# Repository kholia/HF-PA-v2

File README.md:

### HF-PA-v2

VU3CER's `Class-E HF PA` for https://github.com/kholia/Easy-Digital-Beacons-v1
project for 20m band and up. It has (optional) software-controlled variable PA
Output Power.

Supported bands: 80, 60, 40, 30, 20, 17m, and more bands with switchable 'LPF
Module' board.

(July 2021 Update): While this HF PA works as well as the uSDX V1.02 PA and the
QCX+ PA (they all use the same design!), we prefer our new [HF-PA-v3
system](https://github.com/kholia/HF-PA-v3/) PA for its robustness. If you
need a 3W+ @ 14 MHz with high efficiency, this Class-E HF PA design
(`HF-PA-v2`) is the best one ;)

Constraints for the initial PCB prototypes for validating the design:

- PCB is to be homebrewed (laser printer, toner tranfer using iron, etching via FeCl3)

- PCB is single-sided. Only one layer is available for routing.

- BS170 MOSFETs need to be on an edge to allow usage of heatsinks.

- My external `PA150 HF Linear Amplifier` needs 2W minimum to function.

Input: Few milliwatts is fine. Note: Si5351's output is around 8-10mW.

Output: Full-power 3.2W+ @ 13.3v (4S LiFePo4) for 20m band (14.074 MHz) with
around 45-55% efficiency *OR* Safer 2W with reasonable PWM setting for digital
modes!

Note: All screenshots are clickable and zoomable.

Note 2: Active cooling (fan) is recommended for digital modes! You have been
informed ;)

Schematic:

The HF PA has over-voltage ("High-SWR") protection via a `47v zener power-dumping diode`.

PCB renderings:

Socketable version (recommended):

Testing the Triple-Mode PSU + LPF 20m + 3xBS170 @ 13.8v:

LPF schematic (from uSDX PCB by WB2CBA):

Safe power supply module for the PA. It has over-current protection.

Note: This 3D rendering is *only* published to help with the manual layout work
on Zero-PCBs.

Note 2: Various sub-circuits were simulated in LTspice prior to implementation.

### Sample Code

- https://github.com/kholia/uSDX_Beacon

- https://github.com/kholia/Easy-Digital-Beacons-v1

#### O(Current consumption)

The ESP8266 usually draws a peak current of about 250mA after it wakes up and
then more or less constantly draws around 70mA before it goes back to sleep.

DS3231 -> 5mA

Si5351 -> ~50 to 100mA

Upper bound -> 1.4A maximum.

#### BOM

- 1 x SN74ACT00N (TI)

- 3 x BS170 (ON Semi)

- 1 x 7805 Voltage Regulator TO-220 (STMicroelectronics)

- 1 x 7806 Voltage Regulator TO-220 (STMicroelectronics)

- 1 x 1N5822

- 1 x 1N5368B (47V 5W Zener Diode)

- 2 x 0.2 Ohms - 3W Current Sensing Resistor

- 2 x 1k Ohm - 0.25W Metal Film Resistor

- 220uF 25v Electrolytic Capacitor

- 5 x 100nF (104) Ceramic Capacitor

- 1 x 10nF (103) Ceramic Capacitor

- 1 x BD140 Transistor

- 1 x TIP42 Darlington Transistor

- 3 x T37-6 - Yellow Toroid, 1 x T37-2 - Red Toroid (LPF)

- 2 x 180pf, 2 x 390pf, 1 x 30pF NP0 Ceramic Capacitors (LPF caps, Kemet)

- 3 meters - Copper Magnetic Winding Wire (24 AWG - 25 SWG)

- Misc: Connectors, Zero PCB, Various Consumables

- Tools: LCR-T4 Meter (for measuring things), RF Power Meter

Tip: Buy in bulk for better pricing, and for getting spares for the "junk box".

#### 20m LPF Module Details

- L1 - T37-6 / 16 turns
- L2 - T37-6 / 17 turns
- L3 - T37-6 / 16 turns
- L4 - T37-2 / 10 turns
- C1 - 180pf
- C2 - 390pf
- C3 - 390pf
- C4 - 180pf
- C5 - 30pf

Borrowed from QCX manual and uSDX WB2CBA PCB documentation.

#### BOM + Equipment Sources

- https://www.semikart.com/ (BS170, NP0 LPF caps - Kemet and others, Aavid DIP-14/16 Heat Sinks)

- https://www.semikart.com/search/SN74ACT00N

- https://robu.in/product/0-2-ohm-3w-surface-mount-sense-resistor-pack-of-3/

- https://www.electronicscomp.com/

  - BS170, regular caps, ST voltage regulators

  - TIP42, BD140

- https://www.electroncomponents.com/ (transistors, connectors, consumables, misc)

- https://www.sunrom.com/ (regular ceramic caps)

- https://projectpoint.in/

  - Transistors, regular caps, voltage regulators, MFR resistors, misc

  - Copper Magnetic Winding Wire

- https://www.bhagwatilightingindustries.com (Thermal Adhesive Paste)

- https://www.sunrom.com/p/254mm-40x1-female-socket-strip-machine-round-pins

  `SIP Sockets 1A`

- eBay (`gr_makis`) - Toroids

- [LCR-T4 LCR Meter](https://www.techtonics.in/lcr-t4-12864-lcd-graphical-transistor-tester-resistance-capacitance-esr-scr-meter)

### Notes

- The `CDIL 2N3904` TO-92 transistor has `CT2N 3904 LS` marking on it.

  `CT` -> `Continental... Device India Ltd (CDIL)`

- `Burnt` BS170 MOSFETs typically have their `Drain` and `Gate` shorted (Pin 1 and Pin 2 respectively).

- Use `SIP sockets` to avoid accidentally killing the MOSFETs via ESD (during probing, soldering, etc).

- PCB test: Remove the MOSFETS (keep everything else connected) and measure the
  resistance between the `Gate Pin` and `Ground`. It should show `OL (Open Line)`.

### Tips

- BS170 MOSFETs are very sensitive with regards to ESD and high soldering
  temperatures.

  Use best practices when dealing with BS170 MOSFETs and perhaps always ;)

#### References

- https://github.com/kholia/uSDX_Beacon
- https://github.com/agustinmartino/wsjt_transceiver
- http://hyse.org/pdf/www.aoc.nrao.edu/~pharden/hobby/_ClassDEF1.pdf
- http://hyse.org/pdf/www.aoc.nrao.edu/~pharden/hobby/_ClassDEF2.pdf
- http://thestone.zone/radio/2020/12/13/multi-watt-amplifier.html
- http://thestone.zone/radio/2020/12/18/gate-driver-amplifier.html
- http://thestone.zone/radio/2021/01/14/capacitors.html
- http://thestone.zone/radio/2021/01/16/minor-enhancements.html
- https://www.g0kla.com/scpa/SimpleCheapPA.php
- https://www.linkedin.com/pulse/rf-pcb-design-rules-manufacturing-process-lisa-chu/
- http://thestone.zone/radio/2021/06/04/attenuator.html
- http://thestone.zone/radio/2021/06/05/power-amplifier.html
- https://on7dq.blogspot.com/2020/12/qcx-mini-measurements.html
- https://www.random-science-tools.com/electronics/dBm-Watts-volts.htm
- https://www.mitsubishielectric.com/semiconductors/php/oSearch.php?FOLDER=/product/highfrequency/siliconrf/discrete
- http://www.carnut.info/WSPR_Tx/WSPR_Tx.htm
- https://sites.google.com/view/andy-g0ftd/iron-fist-transmitter
- https://www.dj0abr.de/english/technik/dds/pa.htm
- https://www.qsl.net/py2ohh/
- https://hf5l.pl/en/transceiver-usdx-with-arduino-nano/#

#### Credits

- MTR5B schematic
- PFR-3 design
- Dan Tayloe, N7VE (NC2030 PA design)
- Hans Summers (QCX+)
- Guido PE1NNZ (uSDX)
- WB2CBA (uSDX PCB)
- Tom (AK2B)
- Various uSDX folks
- Chris (G0KLA / AC2CZ) - over-current protection

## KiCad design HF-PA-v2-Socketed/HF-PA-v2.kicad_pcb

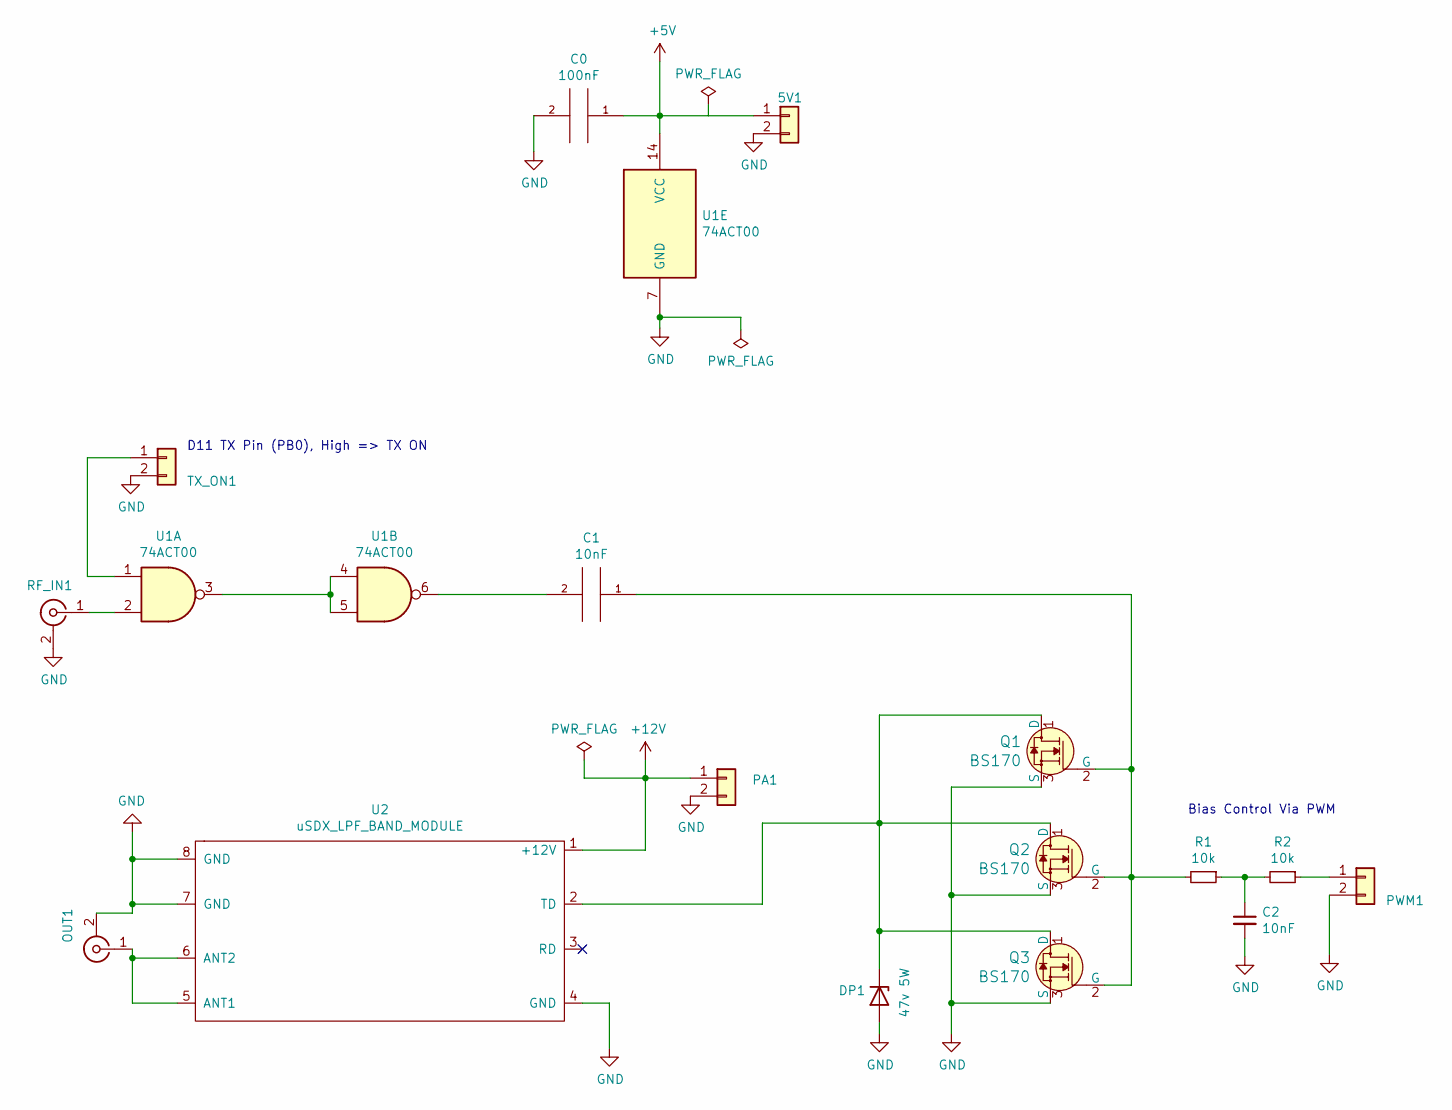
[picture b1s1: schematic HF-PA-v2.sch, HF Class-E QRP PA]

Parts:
5V1: Conn_01x02; PinHeader_1x02_P2.54mm_Vertical
C0: 100nF; C_Disc_D4.3mm_W1.9mm_P5.00mm
C1, C2: 10nF; C_Disc_D4.3mm_W1.9mm_P5.00mm
DP1: 47v 5W; D_DO-201_P5.08mm_Vertical_AnodeUp
OUT1: Conn_Coaxial; SMA_Samtec_SMA-J-P-X-ST-EM1_EdgeMount
PA1: Conn_01x02; PinHeader_1x02_P2.54mm_Vertical
PWM1: Conn_01x02; PinHeader_1x02_P2.54mm_Vertical
Q1, Q2, Q3: BS170; PinSocket_1x03_P2.54mm_Vertical; MPN BS170; Digi-Key_PN BS170-ND
R1, R2: 10k; R_Axial_DIN0204_L3.6mm_D1.6mm_P2.54mm_Vertical
RF_IN1: Conn_Coaxial; SMA_Amphenol_901-144_Vertical
TX_ON1: Conn_01x02; PinHeader_1x02_P2.54mm_Vertical
U1: 74ACT00; DIP-14_W7.62mm_LongPads
U2: uSDX_LPF_BAND_MODULE; uSDX_LPF_Band_Module

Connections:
+5V: 5V1.1, C0.1, U1.14 (VCC)
+12V: PA1.1, U2.1 (+12V)
GND: 5V1.2, C0.2, C2.2, DP1.2 (A), OUT1.2 (Ext), PA1.2, PWM1.2, Q1.3 (S), Q2.3 (S), Q3.3 (S), RF_IN1.2 (Ext), TX_ON1.2, U1.7 (GND), U2.4 (GND), U2.7 (GND), U2.8 (GND); also elsewhere on the board
unnamed 3: C1.1, Q1.2 (G), Q2.2 (G), Q3.2 (G), R1.2; also elsewhere on the board
unnamed: C1.2, U1.6
unnamed: C2.1, R1.1, R2.2
unnamed 6: DP1.1 (K), Q1.1 (D), Q2.1 (D), Q3.1 (D), U2.2 (TD); also elsewhere on the board
unnamed: OUT1.1 (In), U2.5 (ANT1), U2.6 (ANT2)
unnamed: PWM1.1, R2.1
unnamed: RF_IN1.1 (In), U1.2
unnamed: TX_ON1.1, U1.1
unnamed: U1.3, U1.4, U1.5

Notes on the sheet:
D11 TX Pin (PB0), High => TX ON
Bias Control Via PWM

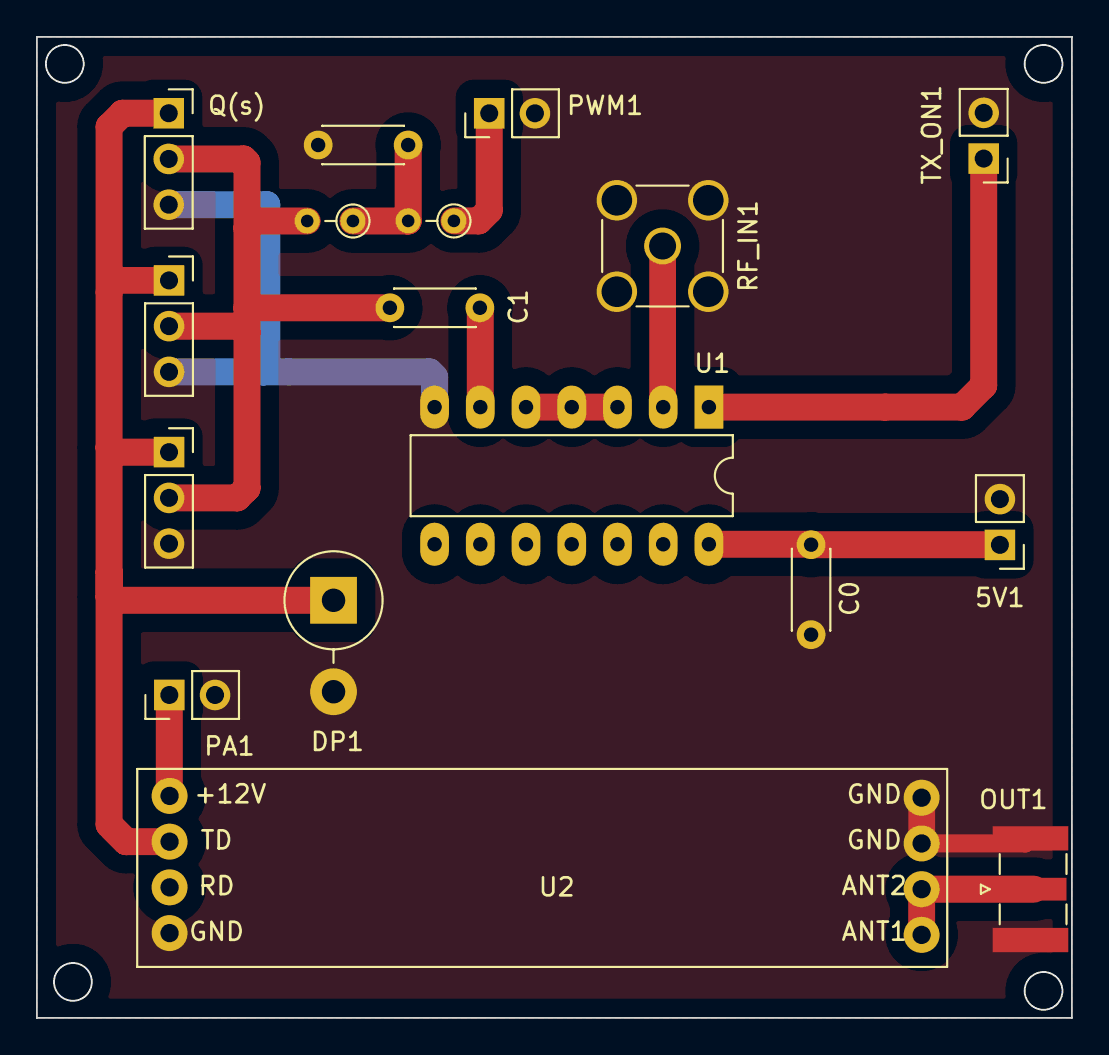
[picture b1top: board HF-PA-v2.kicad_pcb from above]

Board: 2 copper layers, 57.5 x 54.5 mm, 17 parts (0 on the bottom side), 12 nets.

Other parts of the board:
Q(s): BS170; PinSocket_1x03_P2.54mm_Vertical

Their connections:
GND: Q(s).3; also elsewhere on the board
unnamed 3: Q(s).2; also elsewhere on the board
unnamed 6: Q(s).1; also elsewhere on the board

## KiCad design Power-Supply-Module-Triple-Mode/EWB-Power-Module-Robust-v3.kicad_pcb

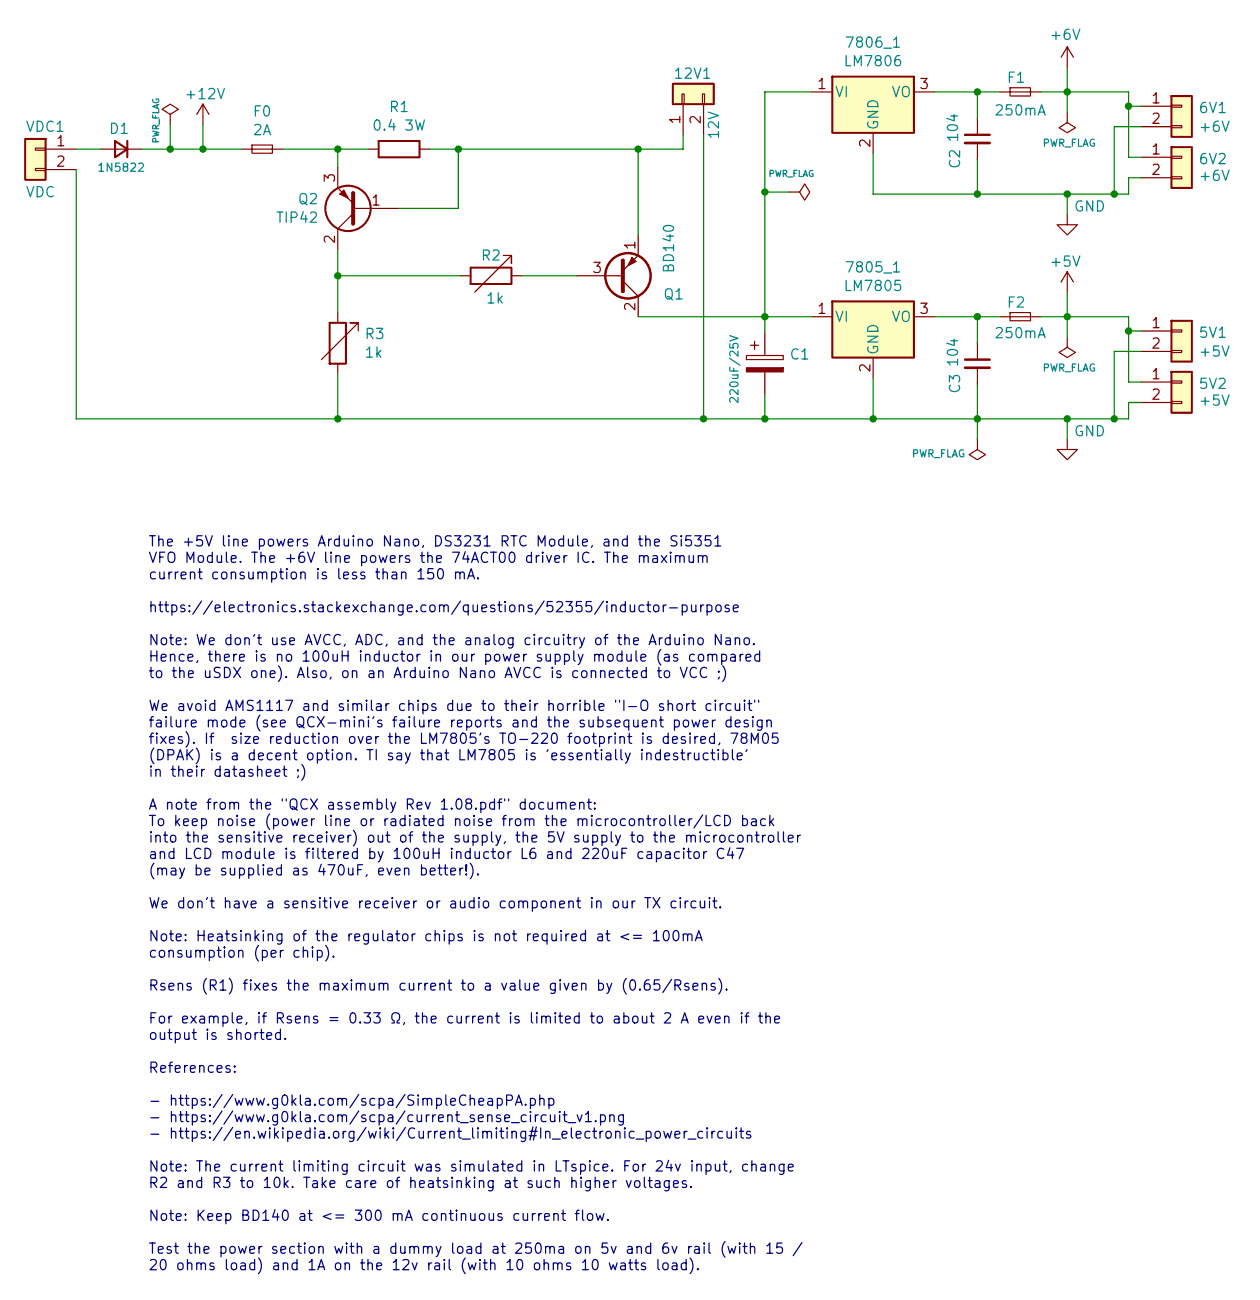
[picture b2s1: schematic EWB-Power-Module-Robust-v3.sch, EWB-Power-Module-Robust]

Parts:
5V1, 5V2: +5V; PinHeader_1x02_P2.54mm_Vertical
6V1, 6V2: +6V; PinHeader_1x02_P2.54mm_Vertical
12V1: 12V; PinHeader_1x02_P2.54mm_Vertical
7805_1: LM7805; TO-220-3_Vertical
7806_1: LM7806; TO-220-3_Vertical
C1: 220uF/25V; CP_Radial_D5.0mm_P2.50mm
C2, C3: 104; C_Disc_D3.4mm_W2.1mm_P2.50mm
D1: 1N5822; D_DO-201AD_P3.81mm_Vertical_KathodeUp
F0: 2A; Fuse_BelFuse_0ZRE0025FF_L9.6mm_W3.8mm
F1, F2: 250mA; Fuse_BelFuse_0ZRE0025FF_L9.6mm_W3.8mm
Q1: BD140; TO-126-3_Vertical
Q2: TIP42; TO-220-3_Vertical
R1: 0.4 3W; R_2512_6332Metric_Pad1.40x3.35mm_HandSolder
R2, R3: 1k; R_Axial_DIN0207_L6.3mm_D2.5mm_P5.08mm_Vertical
VDC1: VDC; PinHeader_1x02_P2.54mm_Vertical

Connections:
+5V: 5V1.1, 5V2.1, F2.2
+6V: 6V1.1, 6V2.1, F1.2
+12V: D1.1 (K), F0.1
GND: 5V1.2, 5V2.2, 6V1.2, 6V2.2, 12V1.2, 7805_1.2 (GND), 7806_1.2 (GND), C1.2, C2.2, C3.2, R3.2, VDC1.2
unnamed: 12V1.1, Q1.1 (E), Q2.1 (B), R1.1
unnamed: 7805_1.1 (VI), 7806_1.1 (VI), C1.1, Q1.2 (C)
unnamed: 7805_1.3 (VO), C3.1, F2.1
unnamed: 7806_1.3 (VO), C2.1, F1.1
unnamed: D1.2 (A), VDC1.1
unnamed: F0.2, Q2.3 (E), R1.2
unnamed: Q1.3 (B), R2.1
unnamed: Q2.2 (C), R2.2, R3.1

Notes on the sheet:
The +5V line powers Arduino Nano, DS3231 RTC Module, and the Si5351 VFO Module. The +6V line powers the 74ACT00 driver IC. The maximum current consumption is less than 150 mA. https://electronics.stackexchange.com/questions/52355/inductor-purpose Note: We don't use AVCC, ADC, and the analog circuit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

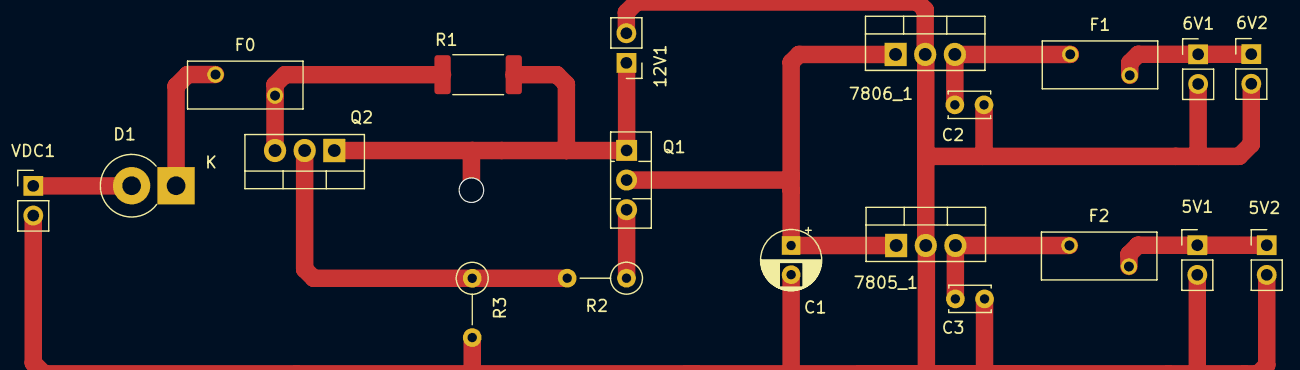
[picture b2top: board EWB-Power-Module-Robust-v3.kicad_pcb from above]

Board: 2 copper layers, 20 parts (0 on the bottom side), 12 nets.
